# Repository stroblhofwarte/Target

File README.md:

# TargetClient
Target(Astronomy) is a small WiFi-Handbox to control a telecope mount via INDI. 
This box is running with battery and does not have any wire to the telecope mount. 
This box consists out of a electronic board, a ESP8266 firmware (arduino IDE) and a 
Qt5 application bridging the handbox to the INDI mount. The handbox provides four keys 
for N,S,W and E, one slew speed key with three LED's and a function key which change 
the N,S,W and E key to Focuser 1 in and out and Focuser 2 in and out 
(not tested yet, I don't have any motor focuser).

# Prerequist (Ubuntu)

```
sudo apt install build-essential
sudo apt install cmake
sudo apt install qt5-default
sudo apt install zlib1g-dev
sudo apt install libcfitsio-dev
```
Installation of the INDI lib development package:
```
sudo apt-add-repository ppa:mutlaqja/ppa
sudo apt update
sudo apt install libindi-dev
```

# How to build

```
cd ~/_develop/

git clone https://github.com/stroblhofwarte/Target.git

mkdir -p ~/_develop/build/targetclient

cd ~/_develop/build/targetclient

cmake -DCMAKE_INSTALL_PREFIX=/usr -DCMAKE_BUILD_TYPE=Release ~/_develop/Target/targetclient

make -j4

sudo cp TargetClient <WHERE/EVER/YOU/WANT>
```

# ASCOM TargetBridge

The new Version of the Target_Astronomy_.ino firmware (from 6.01.2021, ./targetclient/arduino/Target_Astronomy_) is supported by the ASCOM TargetBridge. This version of the firmware is
not supported by the INDI driver anymore. 
The ASCOM TargetBridge adds support for a Win10 based observatory setup. With the TargetBridge application the Target handcontroler 
box can be used to control the mount and the focuser together with the imaging software (e.g. N.I.N.A.). To reach this the ASCOM Hub must
be setup for devices not supporting a multiconnection. The ASCOM Hub must be setup only once. After setup the TargetBridge and/or the imaging
software will startup the hub automatically.

For some convenience four focuser positions (for absolute focuser only) can be marked. This can be used to switch the focal plane between a 
imaging setup with CCD and a visual setup easily.

The ASCOM TargetBridge is written in C# (VisualStudio 2019) and requires the ASCOM development libs to compile properly. 
An precompiled msi package will follow soon.

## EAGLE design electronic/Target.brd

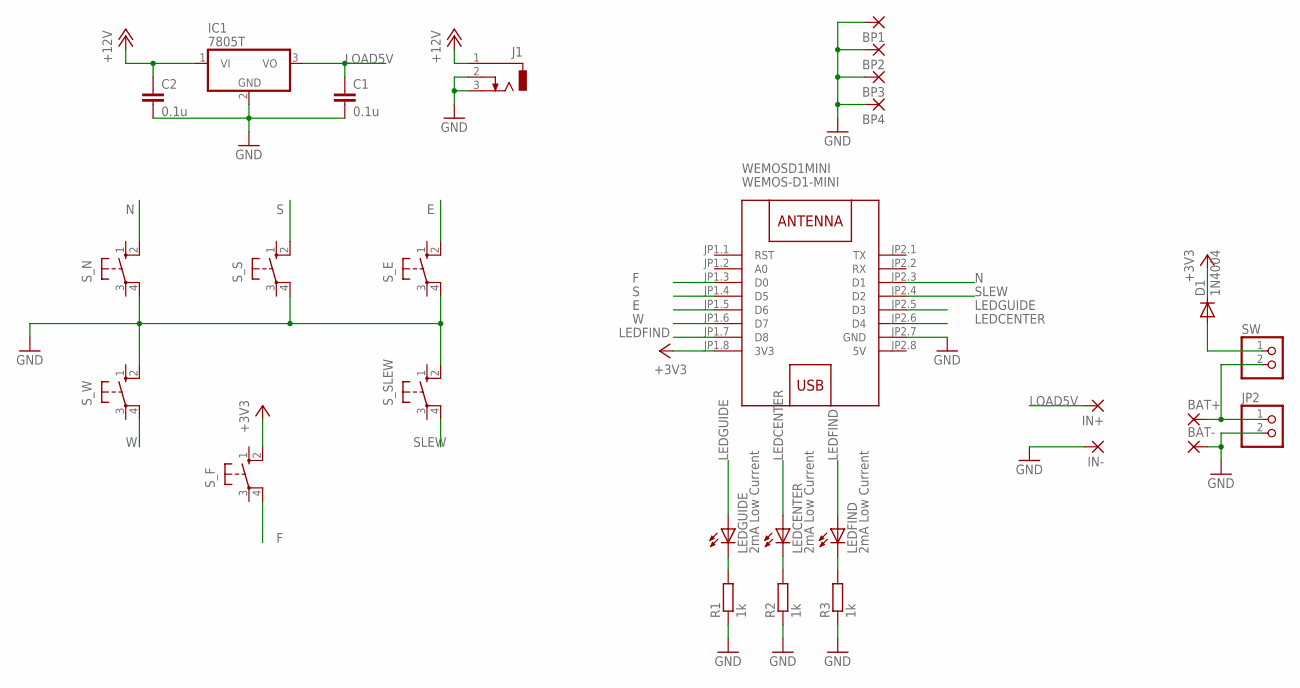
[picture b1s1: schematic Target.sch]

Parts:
BAT+: 2,15/1,0
BAT-: 2,15/1,0
BP1, BP2, BP3, BP4: 3,81/1,4
C1, C2: 0.1u; C025_050-025X075
D1: 1N4004; DO41-10
IC1: 7805T; TO220H
IN+: 2,15/1,0
IN-: 2,15/1,0
J1: DCJ0303
JP2: PINHD-1X2; 1X02
LEDCENTER: 2mA Low Current; LED3MM
LEDFIND: 2mA Low Current; LED3MM
LEDGUIDE: 2mA Low Current; LED3MM
R1, R2, R3: 1k; 0204/7
SW: PINHD-1X2; 1X02
S_E: 40-XX; B3F-40XX
S_F: 40-XX; B3F-40XX
S_N: 40-XX; B3F-40XX
S_S: 40-XX; B3F-40XX
S_SLEW: 40-XX; B3F-40XX
S_W: 40-XX; B3F-40XX
WEMOSD1MINI: WEMOS-D1-MINI

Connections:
5V: WEMOSD1MINI.JP2.8 (5V)
+3V3: D1.C, S_F.2 (S1), WEMOSD1MINI.JP1.8 (3V3)
+12V: C2.1, IC1.1 (VI), J1.1
E: S_E.2 (S1), WEMOSD1MINI.JP1.5 (D6)
F: S_F.4 (P1), WEMOSD1MINI.JP1.3 (D0)
GND: BAT-.1, BP1.1, BP2.1, BP3.1, BP4.1, C1.2, C2.2, IC1.2 (GND), IN-.1, J1.2, J1.3, JP2.2, R1.1, R2.1, R3.1, S_E.4 (P1), S_N.4 (P1), S_S.4 (P1), S_SLEW.2 (S1), S_W.2 (S1), WEMOSD1MINI.JP2.7 (GND)
LEDCENTER: LEDCENTER.A, WEMOSD1MINI.JP2.6 (D4)
LEDFIND: LEDFIND.A, WEMOSD1MINI.JP1.7 (D8)
LEDGUIDE: LEDGUIDE.A, WEMOSD1MINI.JP2.5 (D3)
LOAD5V: C1.1, IC1.3 (VO), IN+.1
N: S_N.2 (S1), WEMOSD1MINI.JP2.3 (D1)
unnamed: LEDGUIDE.K (C), R1.2
unnamed: LEDCENTER.K (C), R2.2
unnamed: LEDFIND.K (C), R3.2
unnamed: BAT+.1, JP2.1, SW.2
unnamed: D1.A, SW.1
S: S_S.2 (S1), WEMOSD1MINI.JP1.4 (D5)
SLEW: S_SLEW.4 (P1), WEMOSD1MINI.JP2.4 (D2)
W: S_W.4 (P1), WEMOSD1MINI.JP1.6 (D7)

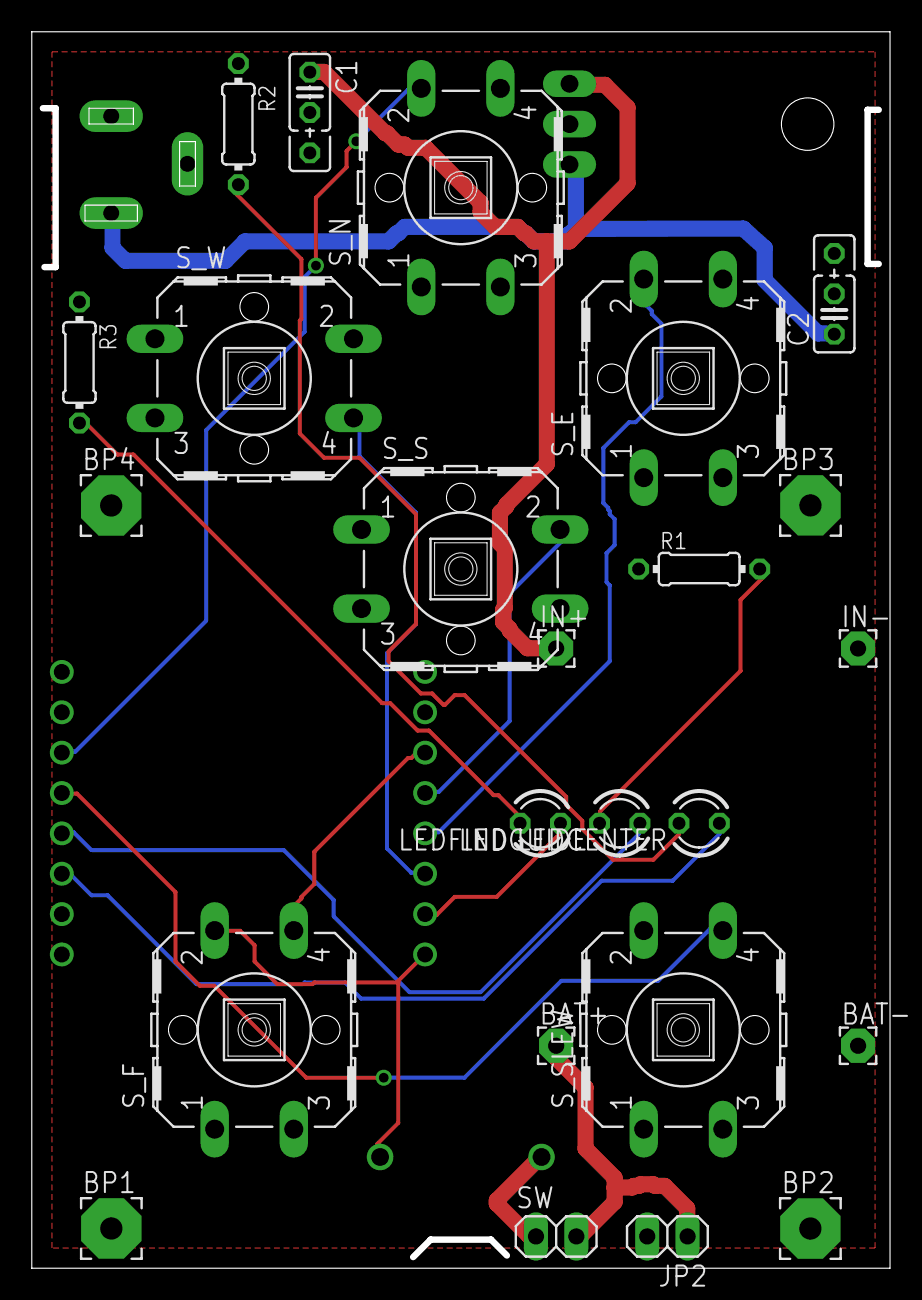
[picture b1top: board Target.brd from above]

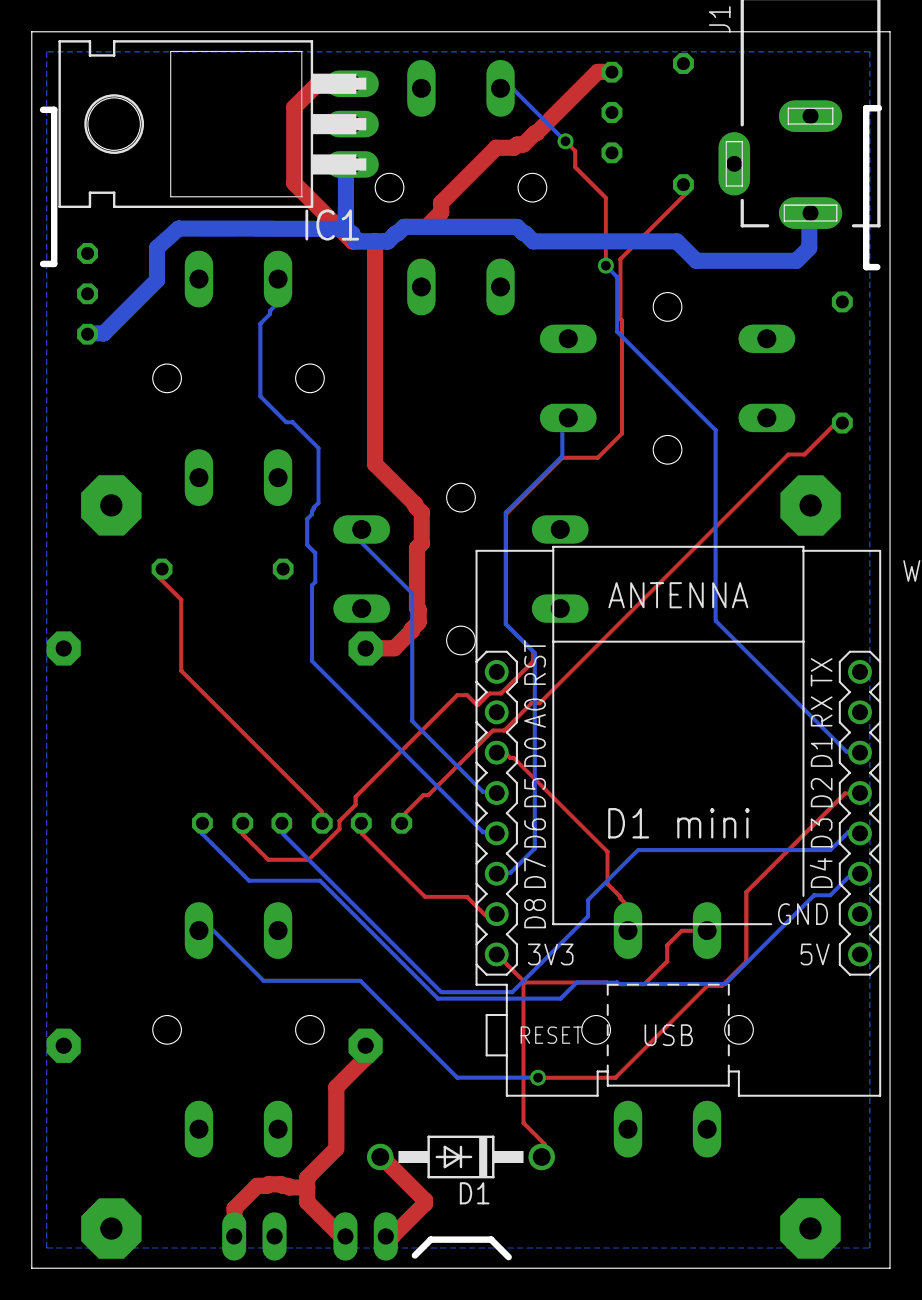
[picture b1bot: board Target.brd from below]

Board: 2 copper layers, 53.6 x 77.4 mm, 28 parts (4 on the bottom side), 18 nets.

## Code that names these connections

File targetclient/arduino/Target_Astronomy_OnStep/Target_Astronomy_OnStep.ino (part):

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#define K_E           D6
#define K_F           D0
#define K_SLEW        D2
#define LEDGUIDE      D8       // OUT
#define LEDCENTER     D3       // OUT
#define LEDFIND       D4       // OUT

#define KEY_NONE      0
#define KEY_N         1
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  pinMode(K_SLEW,   INPUT_PULLUP);
  pinMode(K_F,      INPUT_PULLDOWN_16);

  pinMode(LEDGUIDE,   OUTPUT);
  pinMode(LEDCENTER,  OUTPUT);
  pinMode(LEDFIND,     OUTPUT);

  /************************************/
  
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
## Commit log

2020-08-13 Initial project commit from private GitLab
2020-08-13 Eagle files added
2020-08-13 Add 3D file for the keys
2020-08-13 §D-File for the housing front added
2020-09-13 ESP8266 client for OnStep added
2020-09-15 PDF of the schematic added
2021-01-06 Add TargetBridge as ASCOM bridge for Target
2021-01-06 Add changes for the TargetBridge ASCOM software (Win10). This change is not compatible to the INDI driver anymore.
2021-01-06 Fix wrong date
2021-01-07 Development, what else?
2021-01-07 Remove unessesary files...
2021-01-07 Add first version of a setup project
2021-01-07 Add GPL header
2021-01-14 position number implementation
2021-01-14 Setup V1.1.0

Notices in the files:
targetclient/arduino/Target_Astronomy_OnStep/Target_Astronomy_OnStep.ino:
Licensed under MIT license
parts and their libraries:
diy-modules: Released under the Creative Commons Attribution 4.0 International License: http://creativecommons.org/licenses/by/4.0
